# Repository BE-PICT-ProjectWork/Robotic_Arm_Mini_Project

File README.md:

# Robotic_Arm_Mini_Project
Designed and developed a 6 degrees of freedom robotic arm using an ESP32 microcontroller, PCA9685 servo driver, and PS4 controller. Focused on achieving smooth and precise motion control for reliable object handling, targeting applications in logistics and industrial automation.

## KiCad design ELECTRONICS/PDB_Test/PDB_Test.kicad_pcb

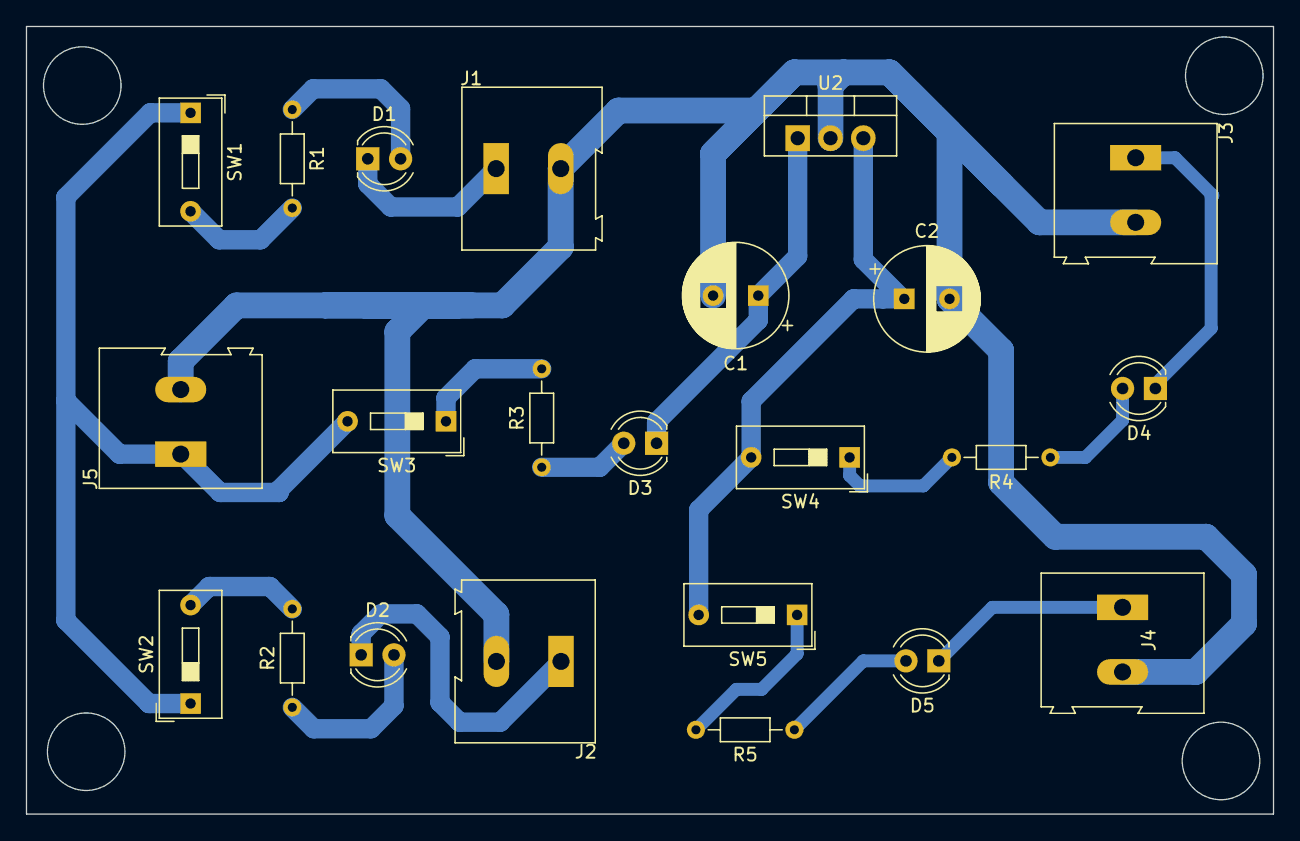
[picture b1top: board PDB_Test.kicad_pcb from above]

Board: 2 copper layers, 96.5 x 61.0 mm, 23 parts (0 on the bottom side), 18 nets.

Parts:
C1: 25V 10uF; CP_Radial_D8.0mm_P3.50mm
C2: 10V 10uF; CP_Radial_D8.0mm_P3.50mm
D1, D2, D3, D4, D5: LED; LED_D4.0mm
J1, J2, J3, J4, J5: Screw_Terminal_01x02; TerminalBlock_Altech_AK300-2_P5.00mm
R1, R2, R3: 1K Ohms; R_Axial_DIN0204_L3.6mm_D1.6mm_P7.62mm_Horizontal
R4, R5: 220 Ohms; R_Axial_DIN0204_L3.6mm_D1.6mm_P7.62mm_Horizontal
SW1, SW2, SW3, SW4, SW5: SW_SPDT; SW_DIP_SPSTx01_Slide_9.78x4.72mm_W7.62mm_P2.54mm
U2: LM7805_TO220; TO-220-3_Vertical

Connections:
Earth: C1.2, C2.2, J1.2, J2.2, J3.2, J4.2, J5.2, U2.2 (GND)
unnamed: D1.2 (A), R1.1
unnamed: D1.1 (K), J1.1
unnamed: D2.2 (A), R2.1
unnamed: D2.1 (K), J2.1
unnamed: D3.2 (A), R3.1
unnamed: C1.1, D3.1 (K), U2.1 (VI)
unnamed: D4.2 (A), R4.1
unnamed: D4.1 (K), J3.1
unnamed: D5.2 (A), R5.1
unnamed: D5.1 (K), J4.1
unnamed: J5.1, SW1.1 (A), SW2.1 (A), SW3.2 (B)
unnamed: R1.2, SW1.2 (B)
unnamed: R2.2, SW2.2 (B)
unnamed: R3.2, SW3.1 (A)
unnamed: R4.2, SW4.1 (A)
unnamed: C2.1, SW4.2 (B), SW5.2 (B), U2.3 (VO)
unnamed: R5.2, SW5.1 (A)

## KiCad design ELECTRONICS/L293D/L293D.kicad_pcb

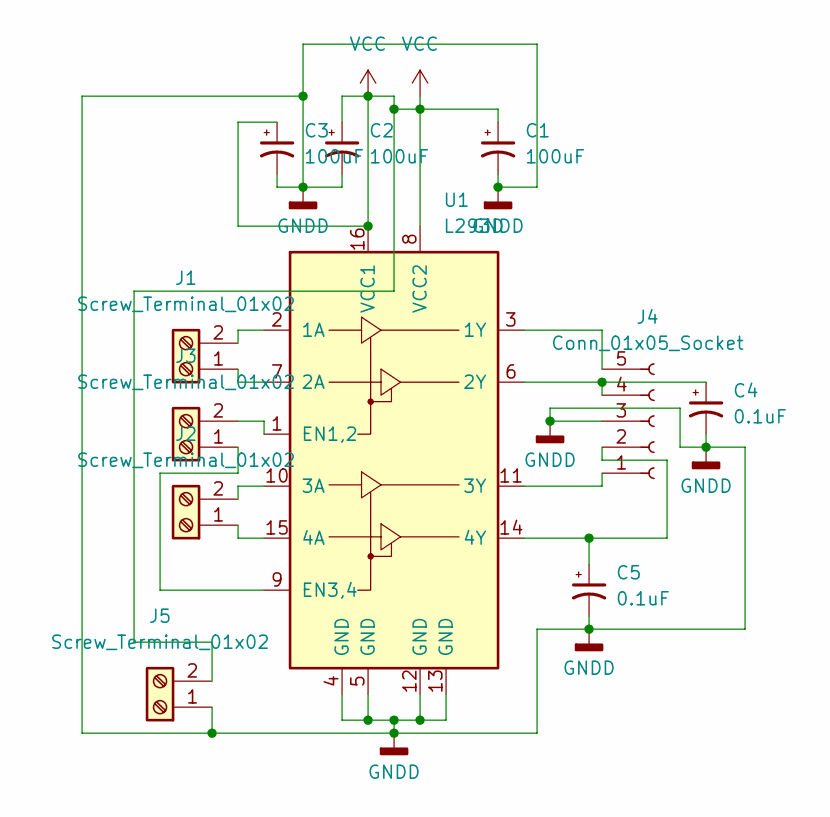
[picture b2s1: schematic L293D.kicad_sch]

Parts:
C1, C2, C3: 100uF; CP_Radial_D5.0mm_P2.50mm
C4, C5: 0.1uF; CP_Radial_D4.0mm_P2.00mm
J1, J2, J3, J5: Screw_Terminal_01x02; TerminalBlock_Altech_AK300-2_P5.00mm
J4: Conn_01x05_Socket; PinSocket_1x05_P2.00mm_Vertical
U1: L293D; DIP-16_W7.62mm

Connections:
GNDD: C1.2, C2.2, C3.2, C4.2, C5.2, J4.3, J5.1, U1.4 (GND), U1.5 (GND), U1.12 (GND), U1.13 (GND)
unnamed: J1.1, U1.7 (2A)
unnamed: J1.2, U1.2 (1A)
unnamed: J2.1, U1.15 (4A)
unnamed: J2.2, U1.10 (3A)
unnamed: J3.1, U1.9 (EN3,4)
unnamed: J3.2, U1.1 (EN1,2)
unnamed: J4.1, U1.11 (3Y)
unnamed: C5.1, J4.2, U1.14 (4Y)
unnamed: C4.1, J4.4, U1.6 (2Y)
unnamed: J4.5, U1.3 (1Y)
VCC: C1.1, C2.1, C3.1, J5.2, U1.8 (VCC2), U1.16 (VCC1)

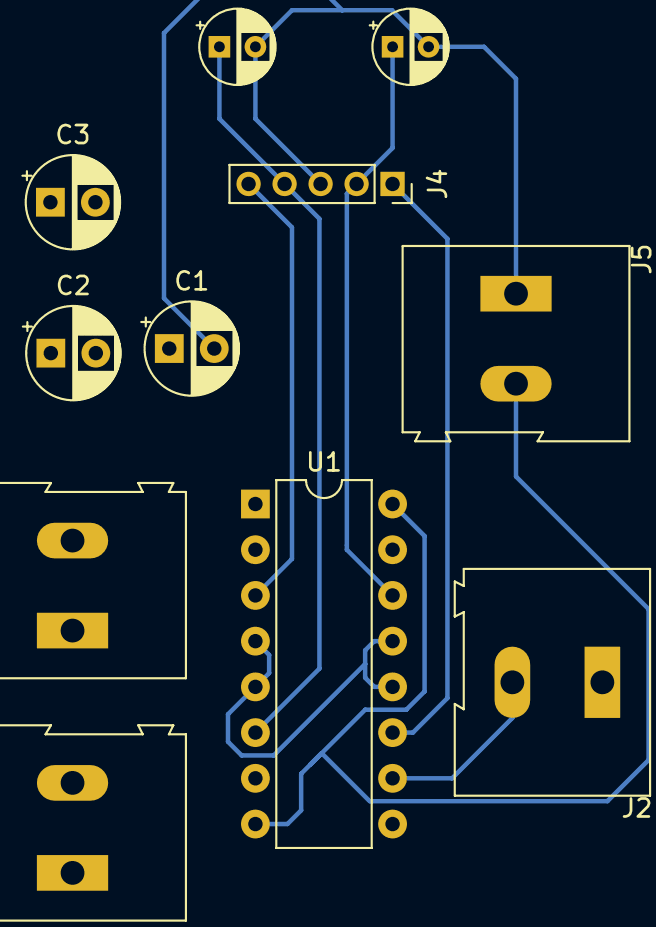
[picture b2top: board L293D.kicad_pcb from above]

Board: 2 copper layers, 11 parts (0 on the bottom side), 12 nets.

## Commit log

2026-01-21 Project Status Updated
